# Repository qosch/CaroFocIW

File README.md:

# CaroFocIW
A small form factor servo inverter for BLDC motors to be mounted directly to the back of the corresponding motor. Intended use in the autonomous 1:10 scale vehicle Carolinchen XI of the Team CDLC (https://www.team-cdlc.de/, german). Firmware compatible with VESC and the custom firmware of the previous iteration. This repository only contains the hardware design.

## Features:
* Field oriented control with sine commutation
* 3× in phase current measurement with oversampling
* 14bit position encoder
* 16kHz sampling rate and PWM frequency
* JST-GH connector with supply and CAN bus interface

## Main components:
Function | used part
------------ | -------------
Microcontroller | STM32F405RGT6
Gate Driver | TLE7185-1E
Current Sensors | 3× ACS71240KEXBLT-010B3
Encoder | AS5048A
CAN Transceiver | TCAN332
Voltage Regulator | LMR16006YQ3
Power MOSFETs | 6× BSZ013NE2LS5I

## Renderings:

## Progress:
* [x] Schematics finished
* [x] Layout finished
* [x] PCB fabricated
* [x] PCB assembled
* [ ] Mechanical assembly finished
* [x] Basic functional tests done
  * [x] Microcontroller working
  * [x] Gate driver working
  * [x] Current sensors working
  * [x] CAN interface working
  * [x] DC link voltage measurement working
  * [x] Angle encoder working
* [x] Fully operational
* [ ] Tested on vehicle
* [ ] Long term real world testing

Link to [Schematics](https://raw.githubusercontent.com/qosch/CaroFocIW/master/Hardware/KiCad/CaroFocIw/Documentation/Schematics.pdf)

Link to [Interactive BOM](http://htmlpreview.github.io/?https://github.com/qosch/CaroFocIW/blob/master/Hardware/KiCad/CaroFocIw/Documentation/BOM.html)

Link to [PCB assembly and test instructions](https://github.com/qosch/CaroFocIW/blob/master/Hardware/KiCad/CaroFocIw/Documentation/PcbAssemblyAndBasicTests.md)

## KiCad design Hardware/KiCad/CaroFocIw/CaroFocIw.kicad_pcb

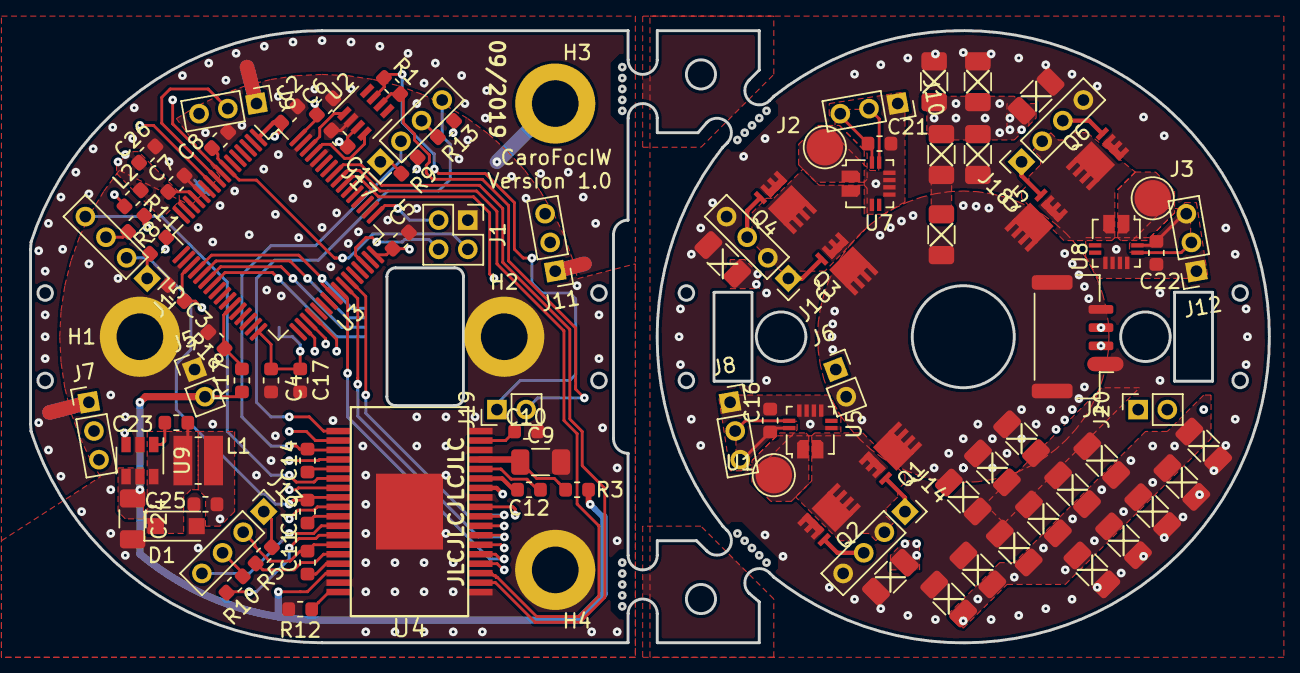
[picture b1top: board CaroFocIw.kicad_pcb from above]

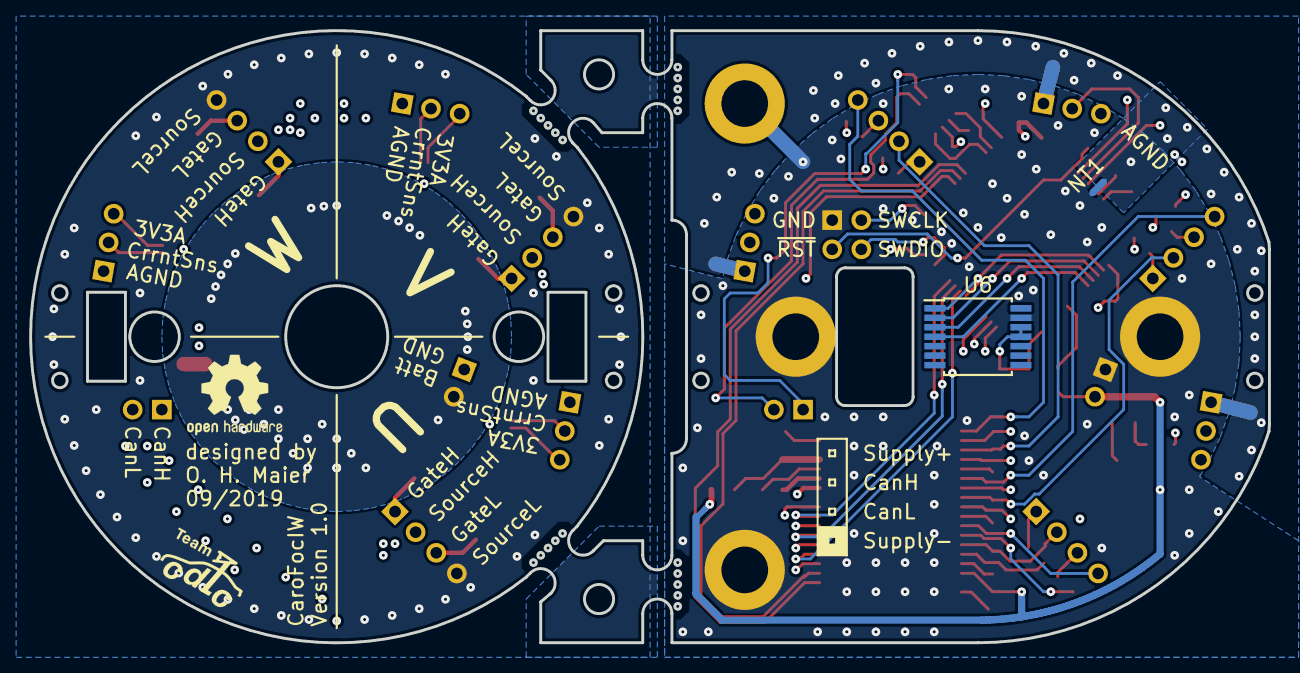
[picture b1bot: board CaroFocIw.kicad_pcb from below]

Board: 4 copper layers, 85.0 x 42.0 mm, 98 parts (2 on the bottom side), 82 nets.

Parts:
C1, C8, C16, C17, C21, C22, C23: 100n; C_0603_1608Metric
C2, C3, C4, C5, C6, C7: 4.7µ, 6.3V; C_0603_1608Metric
C9, C27, C28, C29, C30, C31, C32, C33, C34, C35, C36, C37, C38, C39, C40, C41, C42, C43, C44, C45: 10µ 35V; C_1206_3216Metric
C10, C11, C12, C13, C14: 4.7µ 25V; C_0603_1608Metric
C15, C19, C20, C24: 10μ 35V; C_1206_3216Metric
C25, C26: 10μ 6.3V; C_0603_1608Metric
D1: D_Schottky 1A; D_SOD-123F
H1, H2, H3, H4: MountingHole_Pad; MountingHole_3.2mm_M3_ISO14580_Pad
J1: Conn_01x04; PinHeader_2x02_P2.00mm_Vertical
J2, J3: Conn_01x01; TestPoint_Pad_D2.5mm
J4: Conn_01x04_MountingPin; JST_GH_BM04B-GHS-TBT_1x04-1MP_P1.25mm_Vertical
J5, J19: Conn_01x02; PinHeader_1x02_P2.00mm_Vertical
J6, J20: Conn_01x02; PinSocket_1x02_P2.00mm_Vertical
J7, J9, J11: Conn_01x03; PinHeader_1x03_P2.00mm_Vertical
J8, J10, J12: Conn_01x03; PinSocket_1x03_P2.00mm_Vertical
J13, J15, J17: Conn_01x04; PinHeader_1x04_P2.00mm_Vertical
J14, J16, J18: Conn_01x04; PinSocket_1x04_P2.00mm_Vertical
L1: 10μ 1A; L_Wuerth_MAPI-3015
L2: 10μ 100mA; L_0603_1608Metric
NT1: Net-Tie_2; NetTie-2_SMD_Pad0.5mm
Q1, Q2, Q3, Q4, Q5, Q6: BSZ013NE2LS5I; PG-TSDSON-8-FL
R1: 120; R_0603_1608Metric
R3, R5, R8, R9, R10, R11, R13: 4.7; R_0603_1608Metric
R12, R18: 10k; R_0603_1608Metric
R17: 56k; R_0603_1608Metric
U1: Conn_01x01; TestPoint_Pad_D2.5mm
U2: TCAN332; SOT-23-8
U3: STM32F405RGTx; LQFP-64_10x10mm_P0.5mm
U4: TLE7185-1E; PG-DSO-36-38
U5, U7, U8: ACS711xEXLT-15AB; Allegro_QFN-12-10-1EP_3x3mm_P0.5mm
U6: AS5048A; TSSOP-14_4.4x5mm_P0.65mm
U9: LMR16006YQ3; SOT-23-6

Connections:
3.3VA_U: C16.1, J8.3, U5.10
3.3VA_V: C21.1, J10.3, U7.10
3.3VA_W: C22.1, J12.3, U8.10
+3.3VA: C7.1, C26.1, J7.3, J9.3, J11.3, L2.1, U3.13
+3V3: C1.1, C2.1, C3.1, C4.1, C5.1, C6.1, C17.1, C25.1, L1.1, L2.2, U2.3, U3.1, U3.19, U3.32, U3.48, U3.64, U4.12, U6.11, U6.12, U9.3
+BATT: C15.1, C19.1, C20.1, C27.1, C28.1, C29.1, C30.1, C31.1, C32.1, C33.1, C34.1, C35.1, C36.1, C37.1, C38.1, C39.1, C40.1, C41.1, C42.1, C43.1, C44.1, C45.1, J4.4, J4.MP, J6.2, Q1.3, Q3.3, Q5.3
/Can/CanH: J19.1, R1.1, U2.7
/Can/CanL: J19.2, R1.2, U2.6
/Can/CanRx: U2.4, U3.61
/Can/CanTx: U2.1, U3.62
/CurrentSensingU/AnalogOut: J8.2, U5.9
/CurrentSensingU/PhaseIn: J14.2, Q1.1, Q2.3, U5.2
/CurrentSensingU/PhaseOut: U1.1, U5.1
/CurrentSensingV/AnalogOut: J10.2, U7.9
/CurrentSensingV/PhaseIn: J16.2, Q3.1, Q4.3, U7.2
/CurrentSensingV/PhaseOut: J2.1, U7.1
/CurrentsensingW/AnalogOut: J12.2, U8.9
/CurrentsensingW/PhaseIn: J18.2, Q5.1, Q6.3, U8.2
/CurrentsensingW/PhaseOut: J3.1, U8.1
/DcLinkVoltageSensing/AnalogOut: R17.2, R18.1, U3.27
/Encoder/EncoderMiso: U3.22, U6.3
/Encoder/EncoderMosi: U3.23, U6.4
/Encoder/EncoderSclk: U3.21, U6.2
/Encoder/~EncoderCs: U3.20, U3.40, U6.1
/GateDriver/GateUH: J13.1, R5.1
/GateDriver/GateUHbR: R5.2, U4.32
/GateDriver/GateUL: J13.3, R10.1
/GateDriver/GateVH: J15.1, R8.1
/GateDriver/GateVHbR: R8.2, U4.27
/GateDriver/GateVL: J15.3, R11.1
/GateDriver/GateWH: J17.1, R9.1
/GateDriver/GateWHbR: R9.2, U4.22
/GateDriver/GateWL: J17.3, R13.1
/GateDriver/Gate_U_L_bR: R10.2, U4.30
/GateDriver/Gate_V_L_bR: R11.2, U4.25
/GateDriver/Gate_W_L_bR: R13.2, U4.20
/GateDriver/LogicUL: U3.34, U4.6
/GateDriver/LogicVL: U3.35, U4.8
/GateDriver/LogicWL: U3.36, U4.10
/GateDriver/SourceUH: C11.2, J13.2, U4.31
/GateDriver/SourceUL: J13.4, U4.29
/GateDriver/SourceVH: C13.2, J15.2, U4.26
/GateDriver/SourceVL: J15.4, U4.24
/GateDriver/SourceWH: C14.2, J17.2, U4.21
/GateDriver/SourceWL: J17.4, U4.19
/HalfBridgeU/GateH: J14.1, Q1.2
/HalfBridgeU/GateL: J14.3, Q2.2
/HalfBridgeV/GateH: J16.1, Q3.2
/HalfBridgeV/GateL: J16.3, Q4.2
/HalfBridgeW/GateH: J18.1, Q5.2
/HalfBridgeW/GateL: J18.3, Q6.2
/MCU/CurrentU: J7.2, U3.10
/MCU/CurrentV: J9.2, U3.9
/MCU/CurrentW: J11.2, U3.8
/MCU/GateDriverEnable: U3.55, U4.4
/MCU/LogicUH: U3.41, U4.5
/MCU/LogicVH: U3.42, U4.7
/MCU/LogicWH: U3.43, U4.9
/MCU/SWCLK: J1.3, U3.49
/MCU/SWDIO: J1.4, U3.46
/MCU/~GateDriverErr1: U3.56, U4.3
/MCU/~GateDriverErr2: U3.57, U4.2
/MCU/~RST: C8.1, J1.2, U3.7
/PcbToPcbConnector/CanHB: J4.3, J20.1
/PcbToPcbConnector/CanLB: J4.2, J20.2
AGND_U: C16.2, J8.1, U5.3, U5.5, U5.6, U5.7, U5.8
AGND_V: C21.2, J10.1, U7.3, U7.5, U7.6, U7.7, U7.8
AGND_W: C22.2, J12.1, U8.3, U8.5, U8.6, U8.7, U8.8
BattA: C24.1, J5.2, R3.1, R17.1, U4.34, U9.4, U9.5
GND: C1.2, C2.2, C3.2, C4.2, C5.2, C6.2, C8.2, C9.2, C10.2, C17.2, C24.2, C25.2, D1.2, H1.1, H2.1, H3.1, H4.1, J1.1, J5.1, NT1.1, R12.2, R18.2, U2.2, U3.18, U3.60, U3.63, U4.1, U4.11, U4.16, U4.18, U4.35, U4.37, U6.13, U9.2
GNDA: C7.2, C26.2, J7.1, J9.1, J11.1, NT1.2, U3.12
GNDPWR: C15.2, C19.2, C20.2, C27.2, C28.2, C29.2, C30.2, C31.2, C32.2, C33.2, C34.2, C35.2, C36.2, C37.2, C38.2, C39.2, C40.2, C41.2, C42.2, C43.2, C44.2, C45.2, J4.1, J6.1, J14.4, J16.4, J18.4, Q2.1, Q4.1, Q6.1
unnamed: C9.1, R3.2, U4.15
unnamed: C10.1, U4.17
unnamed: C11.1, U4.33
unnamed: C12.1, U4.13
unnamed: C12.2, U4.14
unnamed: C13.1, U4.28
unnamed: C14.1, U4.23
unnamed: C23.1, U9.1
unnamed: C23.2, D1.1, L1.2, U9.6
unnamed: R12.1, U4.36

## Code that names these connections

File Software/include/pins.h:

/*
 * This file is part of the CaroFoc project.
 */

#include <libopencm3/stm32/gpio.h>

#define DcLinkVoltage_Pin GPIO1
#define DcLinkVoltage_Port GPIOB
#define SpiEncoderNSS_Pin GPIO4
#define SpiEncoderNSS_Port GPIOA
#define SpiEncoderNSS2_Pin GPIO9
#define SpiEncoderNSS2_Port GPIOC
#define SpiEncoderSCK_Pin GPIO5
#define SpiEncoderSCK_Port GPIOA
#define SpiEncoderMISO_Pin GPIO6
#define SpiEncoderMISO_Port GPIOA
#define SpiEncoderMOSI_Pin GPIO7
#define SpiEncoderMOSI_Port GPIOA
#define CurrentU_Pin GPIO2
#define CurrentU_Port GPIOC
#define CurrentV_Pin GPIO1
#define CurrentV_Port GPIOC
#define CurrentW_Pin GPIO0
#define CurrentW_Port GPIOC
#define Gate_U_H_Pin GPIO8
#define Gate_U_H_Port GPIOA
#define Gate_V_H_Pin GPIO9
#define Gate_V_H_Port GPIOA
#define Gate_W_H_Pin GPIO10
#define Gate_W_H_Port GPIOA
#define Gate_U_L_Pin GPIO13
#define Gate_U_L_Port GPIOB
#define Gate_V_L_Pin GPIO14
#define Gate_V_L_Port GPIOB
#define Gate_W_L_Pin GPIO15
#define Gate_W_L_Port GPIOB
#define GateEnable_Pin GPIO3
#define GateEnable_Port GPIOB
#define CanRx_PIN GPIO8
#define CanRx_Port GPIOB
#define CanTx_PIN GPIO9
#define CanTx_Port GPIOB
#define GateErr1_Pin GPIO4
#define GateErr1_Port GPIOB
#define GateErr2_Pin GPIO5
#define GateErr2_Port GPIOB

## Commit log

2019-01-14 Some more layout work
2019-01-14 Added DcLinkVoltageSensing, fixad a bug in schematic, routed remaining nets, got rid of all ERC and DRC errors and changed some mechanical aspects
2019-01-15 Bugfix: placement of one board-to-board connector for current sensing phase U was not aligned with other board. Lots of layout refinements including lower inductance gate switching path, better groun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
2019-01-16 Changed footprint of one inductor, rerouted microcontroller part. Mounting hole placement still needs some thoughts...
2019-02-01 More capacitors, no airwires left (old form factor)
2019-02-04 Smaller form factor -> lots of rerouting needed. Moved gate driver to PCB A
2019-02-05 Some more routing, PCB B almost finished
2019-02-28 more layout
2019-09-07 more routing
2019-09-09 Routing (seems to be) done, should be reviewed before production
2019-09-09 forgot to save
2019-09-12 routing done, some via stitching and panelizing to do
2019-09-12 some panelizing
2019-10-01 preliminary version 1.0
2019-10-03 actual version 1.0, several bugfixes and improvements
2019-10-07 Actual actual version 1.0, some minor changes. PCBs ordered.
2019-10-29 documentation
2019-12-07 added some MCAD files
2020-12-17 bom updated to include traces for debugging
2020-12-19 Added instructions for PCB assembly and first tests
2020-12-19 added some hardware tests
2021-02-22 initial commit of new firmware
2021-02-25 timer 8 init added
2021-02-27 Timer 1 configured and working
2021-02-28 timer 8 configured to run in sync with timer 1
2021-03-04 timers 1 and 8 runnding in sync and 8 generating NCS pulses
